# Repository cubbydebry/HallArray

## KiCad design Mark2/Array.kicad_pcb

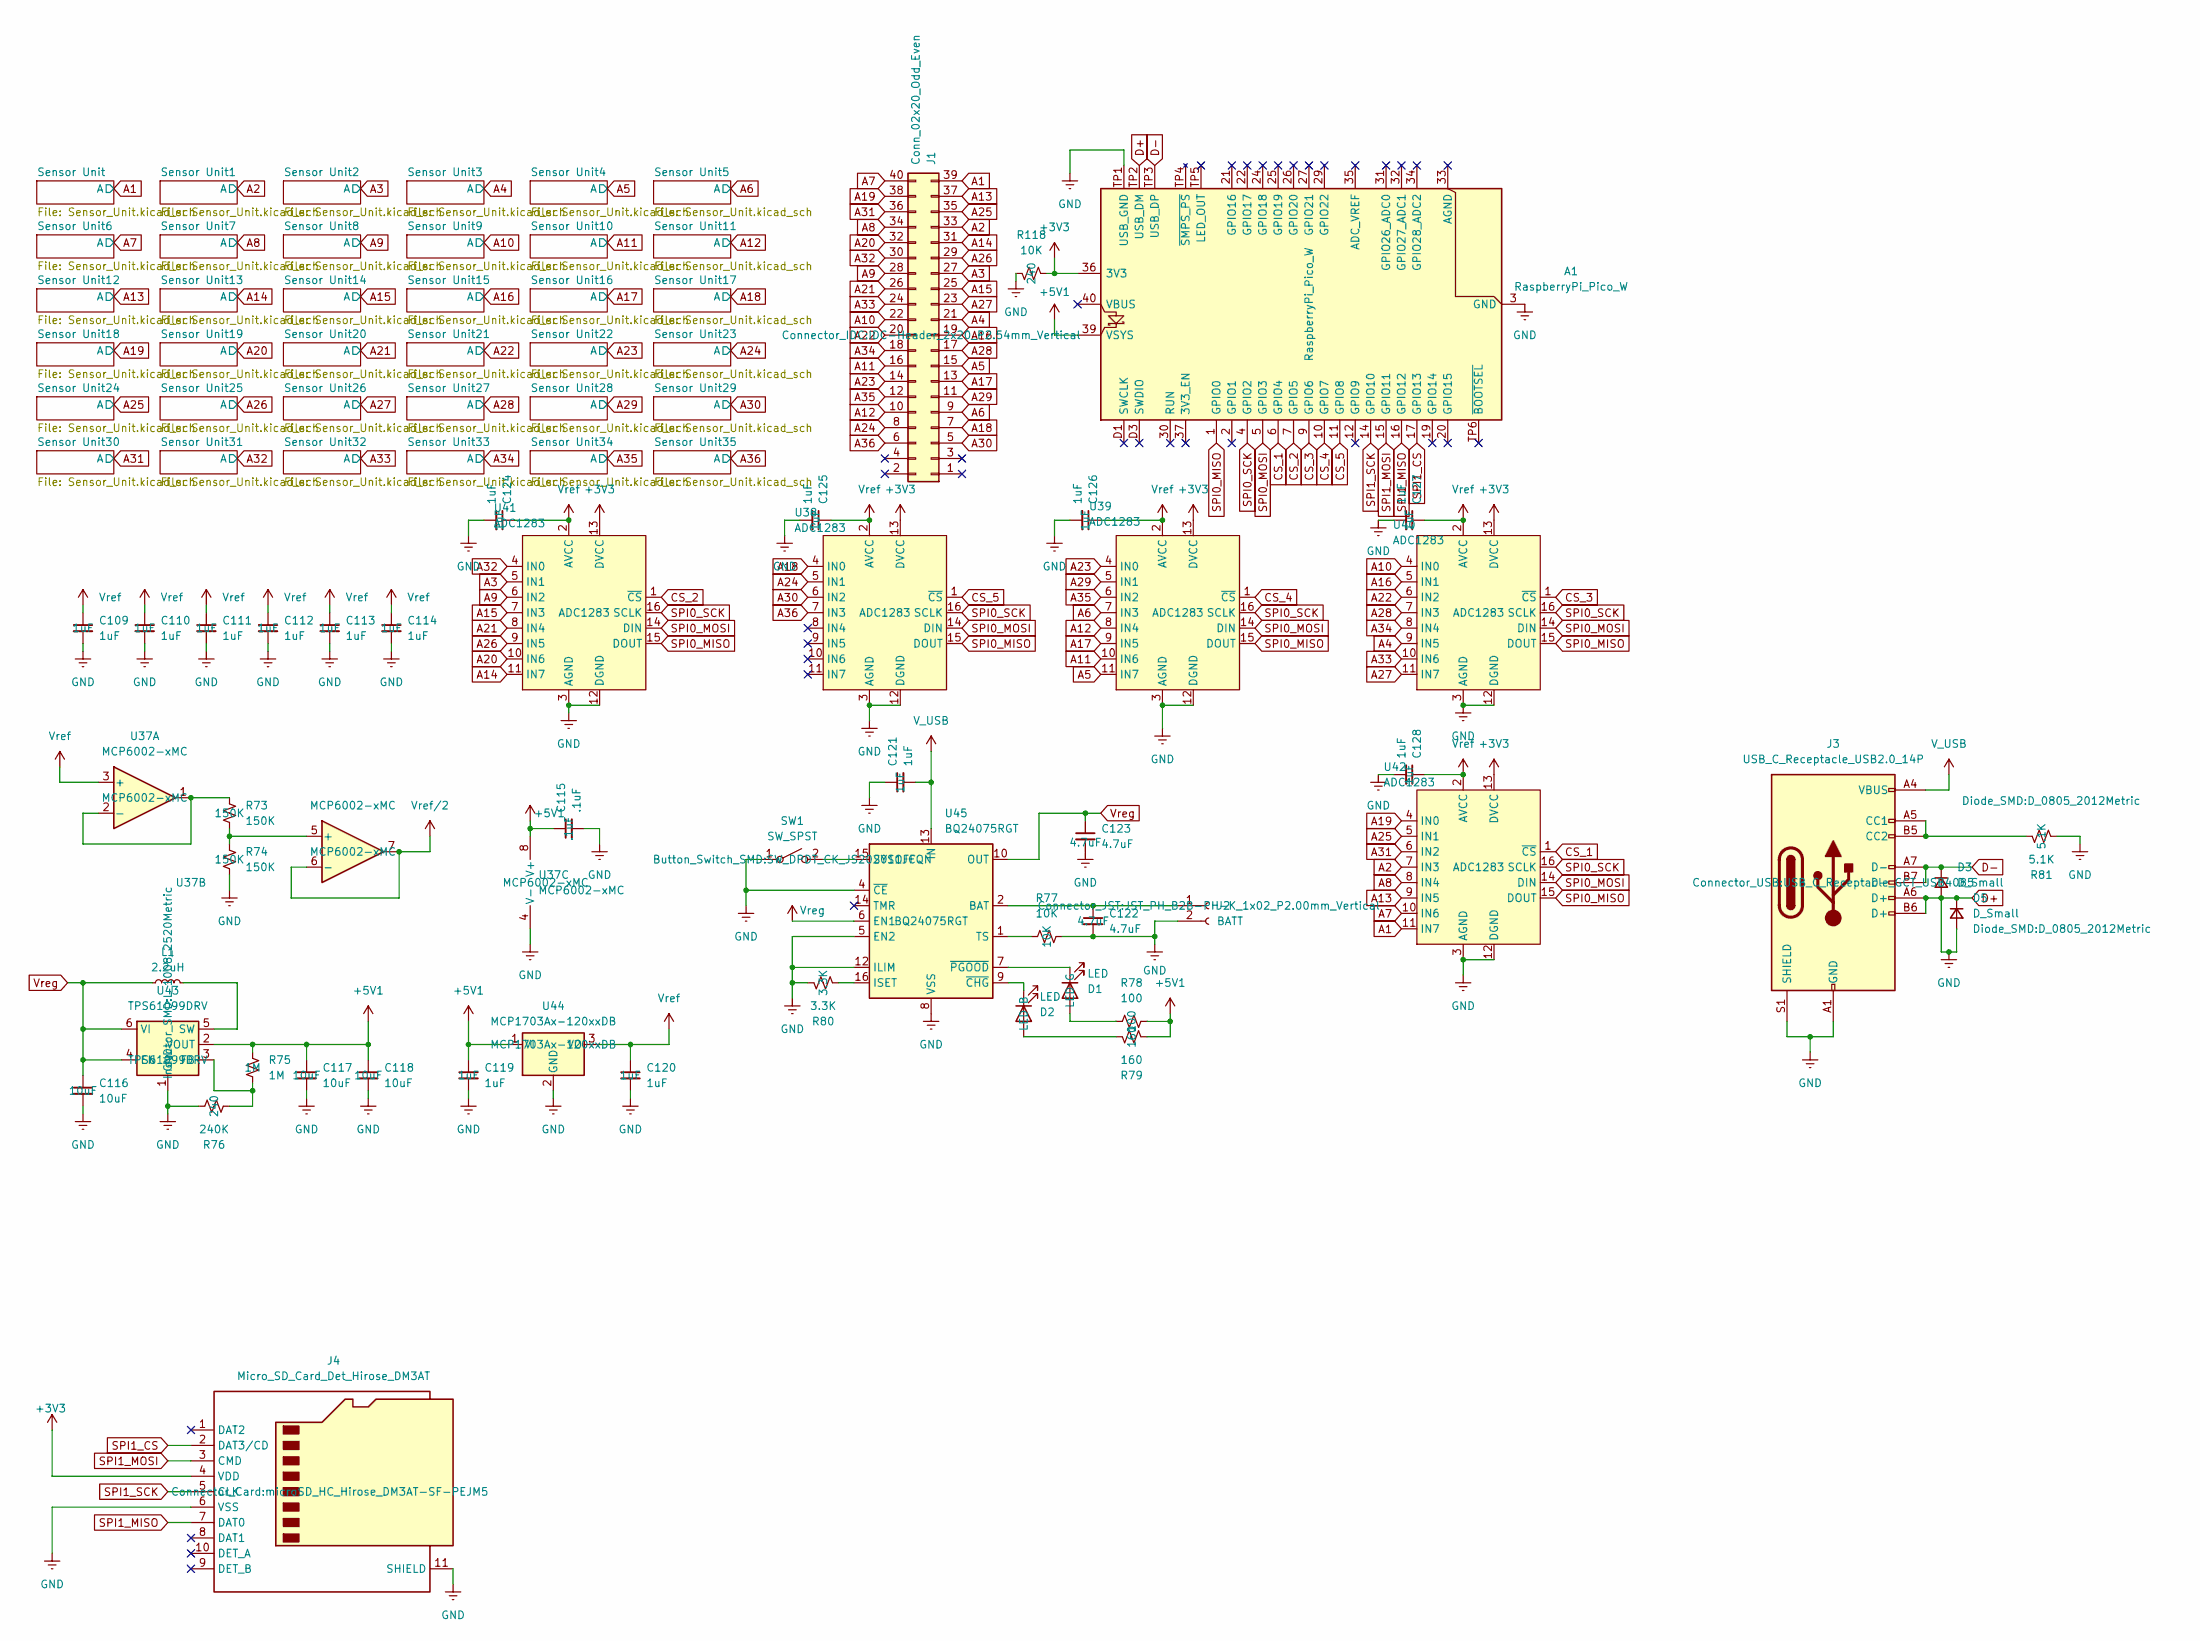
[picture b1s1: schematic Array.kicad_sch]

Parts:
A1: RaspberryPi_Pico_W; RaspberryPi_Pico_W_SMD; Part Number RaspberryPi_Pico_W
C109, C110, C111, C112, C113, C114, C119, C120, C121, C124, C125, C126, C127, C128: 1uF; C_0603_1608Metric; Part Number 1uF
C115: .1uF; C_0603_1608Metric; Part Number .1uF
C116, C117, C118: 10uF; C_0603_1608Metric; Part Number 10uF
C122, C123: 4.7uF; C_0603_1608Metric; Part Number 4.7uF
D1: LED; LED_0805_2012Metric; Part Number LED G
D2: LED; LED_0805_2012Metric; Part Number LED B
D3, D5: D_Small; D_0805_2012Metric; Part Number Diode_SMD:D_0805_2012Metric
J1: Conn_02x20_Odd_Even; IDC-Header_2x20_P2.54mm_Vertical; Part Number Connector_IDC:IDC-Header_2x20_P2.54mm_V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
J2: BATT; JST_PH_B2B-PH-K_1x02_P2.00mm_Vertical; Part Number Connector_JST:JST_PH_B2B-PH-K_1x02_P2.0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
J3: USB_C_Receptacle_USB2.0_14P; USB_C_Receptacle_GCT_USB4085; Part Number Connector_USB:USB_C_Receptacle_GCT_USB4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
J4: Micro_SD_Card_Det_Hirose_DM3AT; microSD_HC_Hirose_DM3AT-SF-PEJM5; Part Number Connector_Card:microSD_HC_Hirose_DM3AT-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
L1: 2.2uH; L_1008_2520Metric; Part Number Inductor_SMD:L_1008_2520Metric
R73, R74: 150K; R_0603_1608Metric; Part Number 150K
R75: 1M; R_0603_1608Metric; Part Number 1M
R76: 240K; R_0603_1608Metric; Part Number 240
R77: 10K; R_0603_1608Metric; Part Number 10K
R78: 100; R_0603_1608Metric; Part Number 100
R79: 160; R_0603_1608Metric; Part Number 160
R80: 3.3K; R_0603_1608Metric; Part Number 3.3K
R81: 5.1K; R_0603_1608Metric; Part Number 5.1K
R118: 10K; R_0603_1608Metric; Part Number 240
SW1: SW_SPST; SW_DPDT_CK_JS202011JCQN; Part Number Button_Switch_SMD:SW_DPDT_CK_JS202011JC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
U37: MCP6002-xMC; DFN-8-1EP_3x2mm_P0.5mm_EP1.75x1.45mm; Part Number MCP6002-xMC
U38, U39, U40, U41, U42: ADC1283; TSSOP-16_4.4x5mm_P0.65mm; Part Number ADC1283
U43: TPS61099DRV; WSON-6-1EP_2x2mm_P0.65mm_EP1x1.6mm; Part Number TPS61099DRV
U44: MCP1703Ax-120xxDB; SOT-223-3_TabPin2; Part Number MCP1703Ax-120xxDB
U45: BQ24075RGT; VQFN-16-1EP_3x3mm_P0.5mm_EP1.6x1.6mm; Part Number BQ24075RGT

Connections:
+3V3: A1.36 (3V3), J4.4 (VDD), R118.1, U38.13 (DVCC), U39.13 (DVCC), U40.13 (DVCC), U41.13 (DVCC), U42.13 (DVCC)
+5V1: A1.39 (VSYS), C115.1, C117.1, C118.1, C119.1, R75.1, R78.1, R79.1, U37.8 (V+), U43.2 (VOUT), U44.1 (VI)
A1: J1.39, U42.11 (IN7); also elsewhere on the board
A2: J1.33, U42.7 (IN3); also elsewhere on the board
A3: J1.27, U41.5 (IN1); also elsewhere on the board
A4: J1.21, U40.9 (IN5); also elsewhere on the board
A5: J1.15, U39.11 (IN7); also elsewhere on the board
A6: J1.9, U39.7 (IN3); also elsewhere on the board
A7: J1.40, U42.10 (IN6); also elsewhere on the board
A8: J1.34, U42.8 (IN4); also elsewhere on the board
A9: J1.28, U41.6 (IN2); also elsewhere on the board
A10: J1.22, U40.4 (IN0); also elsewhere on the board
A11: J1.16, U39.10 (IN6); also elsewhere on the board
A12: J1.10, U39.8 (IN4); also elsewhere on the board
A13: J1.37, U42.9 (IN5); also elsewhere on the board
A14: J1.31, U41.11 (IN7); also elsewhere on the board
A15: J1.25, U41.7 (IN3); also elsewhere on the board
A16: J1.19, U40.5 (IN1); also elsewhere on the board
A17: J1.13, U39.9 (IN5); also elsewhere on the board
A18: J1.7, U38.4 (IN0); also elsewhere on the board
A19: J1.38, U42.4 (IN0); also elsewhere on the board
A20: J1.32, U41.10 (IN6); also elsewhere on the board
A21: J1.26, U41.8 (IN4); also elsewhere on the board
A22: J1.20, U40.6 (IN2); also elsewhere on the board
A23: J1.14, U39.4 (IN0); also elsewhere on the board
A24: J1.8, U38.5 (IN1); also elsewhere on the board
A25: J1.35, U42.5 (IN1); also elsewhere on the board
A26: J1.29, U41.9 (IN5); also elsewhere on the board
A27: J1.23, U40.11 (IN7); also elsewhere on the board
A28: J1.17, U40.7 (IN3); also elsewhere on the board
A29: J1.11, U39.5 (IN1); also elsewhere on the board
A30: J1.5, U38.6 (IN2); also elsewhere on the board
A31: J1.36, U42.6 (IN2); also elsewhere on the board
A32: J1.30, U41.4 (IN0); also elsewhere on the board
A33: J1.24, U40.10 (IN6); also elsewhere on the board
A34: J1.18, U40.8 (IN4); also elsewhere on the board
A35: J1.12, U39.6 (IN2); also elsewhere on the board
A36: J1.6, U38.7 (IN3); also elsewhere on the board
CS_1: A1.6 (GPIO4), U42.1 (~CS)
CS_2: A1.7 (GPIO5), U41.1 (~CS)
CS_3: A1.9 (GPIO6), U40.1 (~CS)
CS_4: A1.10 (GPIO7), U39.1 (~CS)
CS_5: A1.11 (GPIO8), U38.1 (~CS)
unnamed: D1.2 (A), R78.2
unnamed: D1.1 (K), U45.7 (~PGOOD)
unnamed: D2.2 (A), R79.2
unnamed: D2.1 (K), U45.9 (~CHG)
unnamed: C122.1, J2.1, U45.2 (BAT), U45.3 (BAT)
unnamed: J3.A5 (CC1), J3.B5 (CC2), R81.2
unnamed: SW1.2 (B), U45.15 (SYSOFF)
unnamed: R73.1, U37.1, U37.2 (-)
unnamed: R73.2, R74.1, U37.5 (+)
unnamed: R75.2, R76.1, U43.3 (FB)
unnamed: L1.2, U43.5 (SW)
unnamed: R80.1, U45.16 (ISET)
unnamed: R77.2, U45.1 (TS)
SPI0_MISO: A1.1 (GPIO0), U38.15 (DOUT), U39.15 (DOUT), U40.15 (DOUT), U41.15 (DOUT), U42.15 (DOUT)
SPI0_MOSI: A1.5 (GPIO3), U38.14 (DIN), U39.14 (DIN), U40.14 (DIN), U41.14 (DIN), U42.14 (DIN)
SPI0_SCK: A1.4 (GPIO2), U38.16 (SCLK), U39.16 (SCLK), U40.16 (SCLK), U41.16 (SCLK), U42.16 (SCLK)
SPI1_CS: A1.17 (GPIO13), J4.2 (DAT3/CD)
SPI1_MISO: A1.16 (GPIO12), J4.7 (DAT0)
SPI1_MOSI: A1.15 (GPIO11), J4.3 (CMD)
SPI1_SCK: A1.14 (GPIO10), J4.5 (CLK)
V_USB: C121.2, J3.A4 (VBUS), J3.A9 (VBUS), J3.B4 (VBUS), J3.B9 (VBUS), U45.13 (IN)
Vref: C109.1, C110.1, C111.1, C112.1, C113.1, C114.1, C120.1, C124.1, C125.1, C126.1, C127.1, C128.1, U37.3 (+), U38.2 (AVCC), U39.2 (AVCC), U40.2 (AVCC), U41.2 (AVCC), U42.2 (AVCC), U44.3 (VO); also elsewhere on the board
Vref/2: U37.6 (-), U37.7; also elsewhere on the board
Vreg: C116.1, C123.1, L1.1, U43.4 (EN), U43.6 (VI), U45.6 (EN1), U45.10 (OUT), U45.11 (OUT)

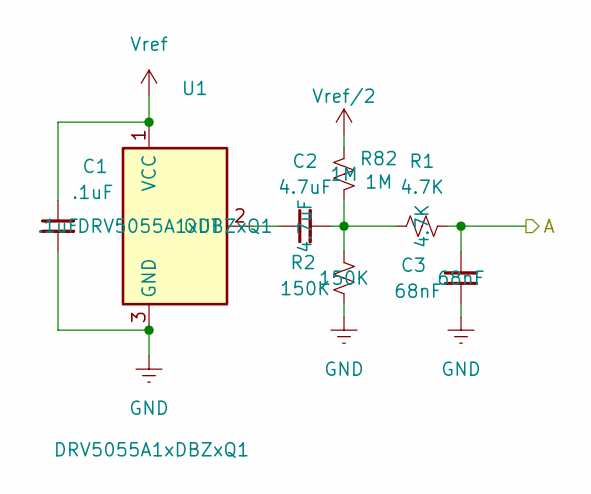
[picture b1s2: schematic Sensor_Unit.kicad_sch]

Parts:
C1: .1uF; C_0603_1608Metric; Part Number .1uF
C2: 4.7uF; C_0603_1608Metric; Part Number 4.7uF
C3: 68nF; C_0603_1608Metric; Part Number 68nF
R1: 4.7K; R_0603_1608Metric; Part Number 4.7K
R2: 150K; R_0603_1608Metric; Part Number 150K
R82: 1M; R_0603_1608Metric; Part Number 1M
U1: DRV5055A1xDBZxQ1; SOT-23; Part Number DRV5055A1xDBZxQ1

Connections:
A1: C3.2, R1.2; also elsewhere on the board
unnamed: C2.2, R1.1, R2.1, R82.2
unnamed: C2.1, U1.2 (OUT)
Vref: C1.1, U1.1 (VCC); also elsewhere on the board
Vref/2: R82.1; also elsewhere on the board

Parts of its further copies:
C4, C7, C10, C13, C16, C19, C20, C21, C22, C23, C24, C37, C38, C39, C40, C41, C42, C55, C56, C57, C58, C59, C60, C73, C74, C75, C76, C77, C78, C91, C92, C93, C94, C95, C96: .1uF; C_0603_1608Metric; Part Number .1uF
C5, C8, C11, C14, C17, C25, C26, C27, C28, C29, C30, C43, C44, C45, C46, C47, C48, C61, C62, C63, C64, C65, C66, C79, C80, C81, C82, C83, C84, C97, C98, C99, C100, C101, C102: 4.7uF; C_0603_1608Metric; Part Number 4.7uF
C6, C9, C12, C15, C18, C31, C32, C33, C34, C35, C36, C49, C50, C51, C52, C53, C54, C67, C68, C69, C70, C71, C72, C85, C86, C87, C88, C89, C90, C103, C104, C105, C106, C107, C108: 68nF; C_0603_1608Metric; Part Number 68nF
R3, R5, R7, R9, R11, R13, R14, R15, R16, R17, R18, R25, R26, R27, R28, R29, R30, R37, R38, R39, R40, R41, R42, R49, R50, R51, R52, R53, R54, R61, R62, R63, R64, R65, R66: 150K; R_0603_1608Metric; Part Number 150K
R4, R6, R8, R10, R12, R19, R20, R21, R22, R23, R24, R31, R32, R33, R34, R35, R36, R43, R44, R45, R46, R47, R48, R55, R56, R57, R58, R59, R60, R67, R68, R69, R70, R71, R72: 4.7K; R_0603_1608Metric; Part Number 4.7K
R83, R84, R85, R86, R87, R88, R89, R90, R91, R92, R93, R94, R95, R96, R97, R98, R99, R100, R101, R102, R103, R104, R105, R106, R107, R108, R109, R110, R111, R112, R113, R114, R115, R116, R117: 1M; R_0603_1608Metric; Part Number 1M
U2, U3, U4, U5, U6, U7, U8, U9, U10, U11, U12, U13, U14, U15, U16, U17, U18, U19, U20, U21, U22, U23, U24, U25, U26, U27, U28, U29, U30, U31, U32, U33, U34, U35, U36: DRV5055A1xDBZxQ1; SOT-23; Part Number DRV5055A1xDBZxQ1

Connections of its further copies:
A2: C6.2, R4.2; also elsewhere on the board
A3: C9.2, R6.2; also elsewhere on the board
A4: C12.2, R8.2; also elsewhere on the board
A5: C15.2, R10.2; also elsewhere on the board
A6: C18.2, R12.2; also elsewhere on the board
A7: C31.2, R19.2; also elsewhere on the board
A8: C32.2, R23.2; also elsewhere on the board
A9: C33.2, R21.2; also elsewhere on the board
A10: C34.2, R20.2; also elsewhere on the board
A11: C35.2, R22.2; also elsewhere on the board
A12: C36.2, R24.2; also elsewhere on the board
A13: C49.2, R31.2; also elsewhere on the board
A14: C50.2, R35.2; also elsewhere on the board
A15: C51.2, R33.2; also elsewhere on the board
A16: C52.2, R32.2; also elsewhere on the board
A17: C53.2, R34.2; also elsewhere on the board
A18: C54.2, R36.2; also elsewhere on the board
A19: C67.2, R43.2; also elsewhere on the board
A20: C68.2, R47.2; also elsewhere on the board
A21: C69.2, R45.2; also elsewhere on the board
A22: C70.2, R44.2; also elsewhere on the board
A23: C71.2, R46.2; also elsewhere on the board
A24: C72.2, R48.2; also elsewhere on the board
A25: C85.2, R55.2; also elsewhere on the board
A26: C86.2, R59.2; also elsewhere on the board
A27: C87.2, R57.2; also elsewhere on the board
A28: C88.2, R56.2; also elsewhere on the board
A29: C89.2, R58.2; also elsewhere on the board
A30: C90.2, R60.2; also elsewhere on the board
A31: C103.2, R67.2; also elsewhere on the board
A32: C104.2, R71.2; also elsewhere on the board
A33: C105.2, R69.2; also elsewhere on the board
A34: C106.2, R68.2; also elsewhere on the board
A35: C107.2, R70.2; also elsewhere on the board
A36: C108.2, R72.2; also elsewhere on the board
unnamed: C5.2, R3.1, R4.1, R83.2
unnamed: C8.2, R5.1, R6.1, R84.2
unnamed: C11.2, R7.1, R8.1, R85.2
unnamed: C14.2, R9.1, R10.1, R86.2
unnamed: C17.2, R11.1, R12.1, R87.2
unnamed: C25.2, R15.1, R23.1, R89.2
unnamed: C26.2, R17.1, R21.1, R90.2
unnamed: C27.2, R13.1, R20.1, R91.2
unnamed: C28.2, R18.1, R22.1, R92.2
unnamed: C29.2, R16.1, R24.1, R93.2
unnamed: C30.2, R14.1, R19.1, R88.2
unnamed: C43.2, R27.1, R35.1, R95.2
unnamed: C44.2, R29.1, R33.1, R96.2
unnamed: C45.2, R25.1, R32.1, R97.2
unnamed: C46.2, R30.1, R34.1, R98.2
unnamed: C47.2, R28.1, R36.1, R99.2
unnamed: C48.2, R26.1, R31.1, R94.2
unnamed: C61.2, R39.1, R47.1, R101.2
unnamed: C62.2, R41.1, R45.1, R102.2
unnamed: C63.2, R37.1, R44.1, R103.2
unnamed: C64.2, R42.1, R46.1, R104.2
unnamed: C65.2, R40.1, R48.1, R105.2
unnamed: C66.2, R38.1, R43.1, R100.2
unnamed: C79.2, R51.1, R59.1, R107.2
unnamed: C80.2, R53.1, R57.1, R108.2
unnamed: C81.2, R49.1, R56.1, R109.2
unnamed: C82.2, R54.1, R58.1, R110.2
unnamed: C83.2, R52.1, R60.1, R111.2
unnamed: C84.2, R50.1, R55.1, R106.2
unnamed: C97.2, R63.1, R71.1, R113.2
unnamed: C98.2, R65.1, R69.1, R114.2
unnamed: C99.2, R61.1, R68.1, R115.2
unnamed: C100.2, R66.1, R70.1, R116.2
unnamed: C101.2, R64.1, R72.1, R117.2
unnamed: C102.2, R62.1, R67.1, R112.2
unnamed: C5.1, U2.2 (OUT)
unnamed: C8.1, U3.2 (OUT)
unnamed: C11.1, U4.2 (OUT)
unnamed: C14.1, U5.2 (OUT)
unnamed: C17.1, U6.2 (OUT)
unnamed: C30.1, U7.2 (OUT)
unnamed: C25.1, U8.2 (OUT)
unnamed: C26.1, U9.2 (OUT)
unnamed: C27.1, U10.2 (OUT)
unnamed: C28.1, U11.2 (OUT)
unnamed: C29.1, U12.2 (OUT)
unnamed: C48.1, U13.2 (OUT)
unnamed: C43.1, U14.2 (OUT)
unnamed: C44.1, U15.2 (OUT)
unnamed: C45.1, U16.2 (OUT)
unnamed: C46.1, U17.2 (OUT)
unnamed: C47.1, U18.2 (OUT)
unnamed: C66.1, U19.2 (OUT)
unnamed: C61.1, U20.2 (OUT)
unnamed: C62.1, U21.2 (OUT)
unnamed: C63.1, U22.2 (OUT)
unnamed: C64.1, U23.2 (OUT)
unnamed: C65.1, U24.2 (OUT)
unnamed: C84.1, U25.2 (OUT)
unnamed: C79.1, U26.2 (OUT)
unnamed: C80.1, U27.2 (OUT)
unnamed: C81.1, U28.2 (OUT)
unnamed: C82.1, U29.2 (OUT)
unnamed: C83.1, U30.2 (OUT)
unnamed: C102.1, U31.2 (OUT)
unnamed: C97.1, U32.2 (OUT)
unnamed: C98.1, U33.2 (OUT)
unnamed: C99.1, U34.2 (OUT)
unnamed: C100.1, U35.2 (OUT)
unnamed: C101.1, U36.2 (OUT)
Vref: C4.1, C7.1, C10.1, C13.1, C16.1, C19.1, C20.1, C21.1, C22.1, C23.1, C24.1, C37.1, C38.1, C39.1, C40.1, C41.1, C42.1, C55.1, C56.1, C57.1, C58.1, C59.1, C60.1, C73.1, C74.1, C75.1, C76.1, C77.1, C78.1, C91.1, C92.1, C93.1, C94.1, C95.1, C96.1, U2.1 (VCC), U3.1 (VCC), U4.1 (VCC), U5.1 (VCC), U6.1 (VCC), U7.1 (VCC), U8.1 (VCC), U9.1 (VCC), U10.1 (VCC), U11.1 (VCC), U12.1 (VCC), U13.1 (VCC), U14.1 (VCC), U15.1 (VCC), U16.1 (VCC), U17.1 (VCC), U18.1 (VCC), U19.1 (VCC), U20.1 (VCC), U21.1 (VCC), U22.1 (VCC), U23.1 (VCC), U24.1 (VCC), U25.1 (VCC), U26.1 (VCC), U27.1 (VCC), U28.1 (VCC), U29.1 (VCC), U30.1 (VCC), U31.1 (VCC), U32.1 (VCC), U33.1 (VCC), U34.1 (VCC), U35.1 (VCC), U36.1 (VCC); also elsewhere on the board
Vref/2: R83.1, R84.1, R85.1, R86.1, R87.1, R88.1, R89.1, R90.1, R91.1, R92.1, R93.1, R94.1, R95.1, R96.1, R97.1, R98.1, R99.1, R100.1, R101.1, R102.1, R103.1, R104.1, R105.1, R106.1, R107.1, R108.1, R109.1, R110.1, R111.1, R112.1, R113.1, R114.1, R115.1, R116.1, R117.1; also elsewhere on the board

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
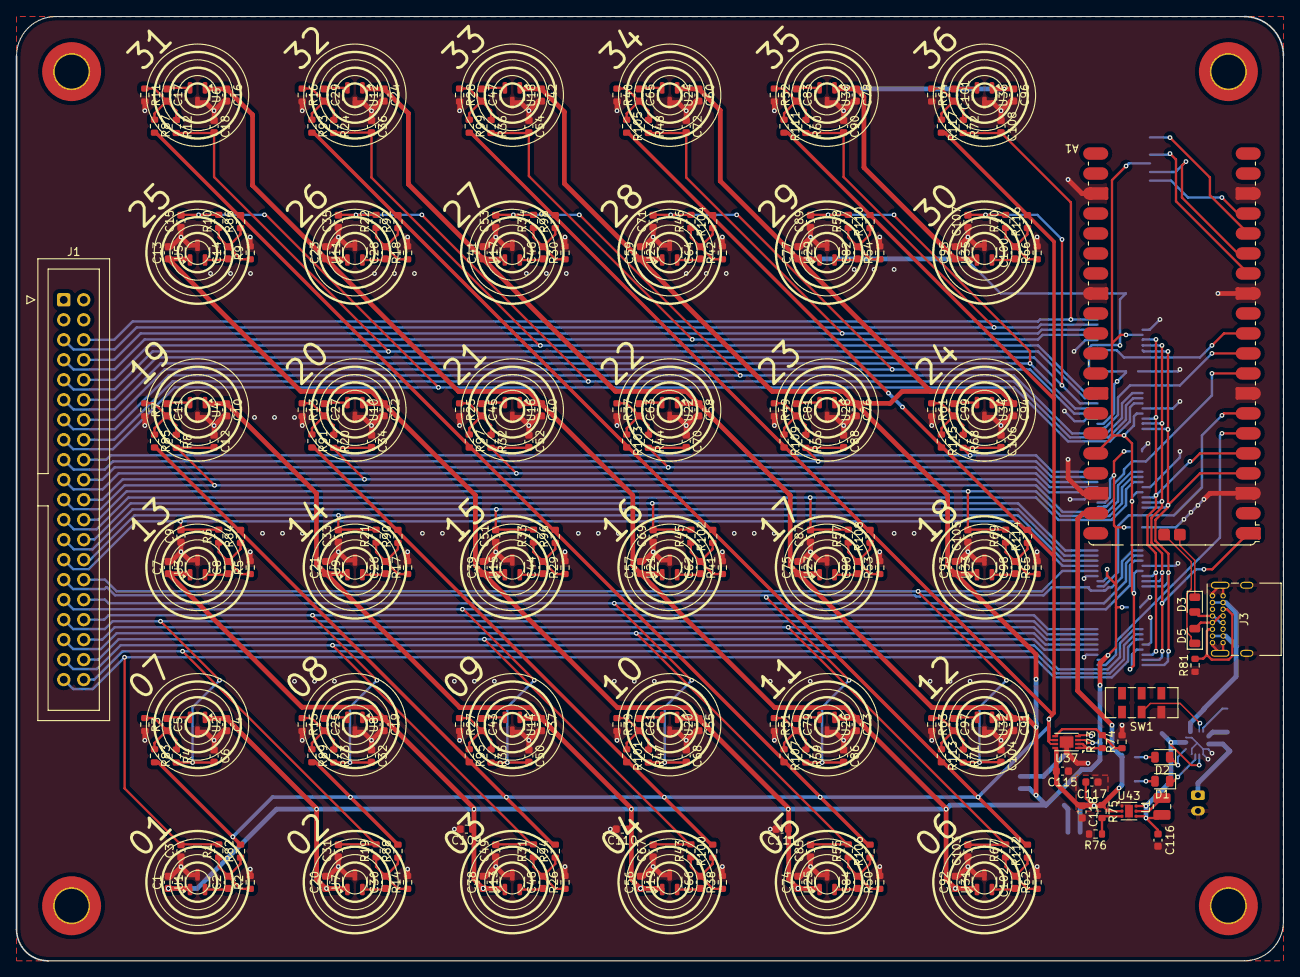
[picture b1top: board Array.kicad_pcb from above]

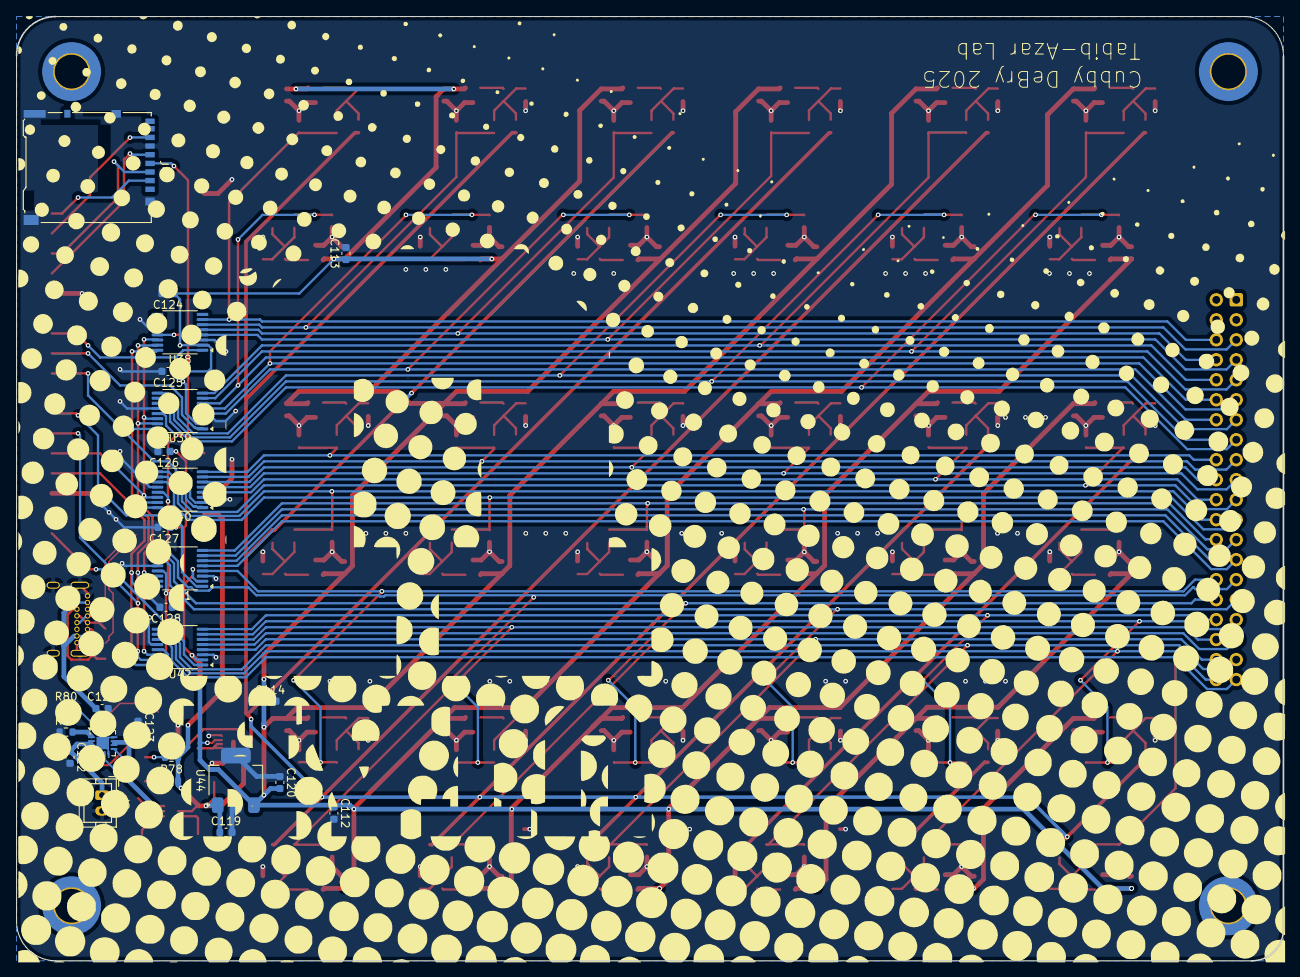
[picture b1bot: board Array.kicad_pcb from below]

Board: 2 copper layers, 161.0 x 120.0 mm, 301 parts (26 on the bottom side), 144 nets.

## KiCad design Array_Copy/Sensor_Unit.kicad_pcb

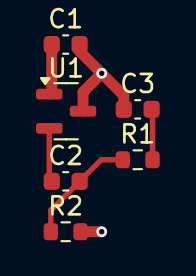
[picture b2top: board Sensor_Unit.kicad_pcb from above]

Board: 2 copper layers, 6 parts (0 on the bottom side), 5 nets.

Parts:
C1: .1uF; C_0603_1608Metric
C2: 1uF; C_0603_1608Metric
C3: 68nF; C_0603_1608Metric
R1: 4.7K; R_0603_1608Metric
R2: 150K; R_0603_1608Metric
U1: DRV5055A1xDBZxQ1; SOT-23

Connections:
+3V3: C1.1, U1.1 (VCC)
A1: C3.2, R1.2
GND: C1.2, C3.1, R2.2, U1.3 (GND)
unnamed: C2.1, U1.2 (OUT)
Vref/2: C2.2, R1.1, R2.1

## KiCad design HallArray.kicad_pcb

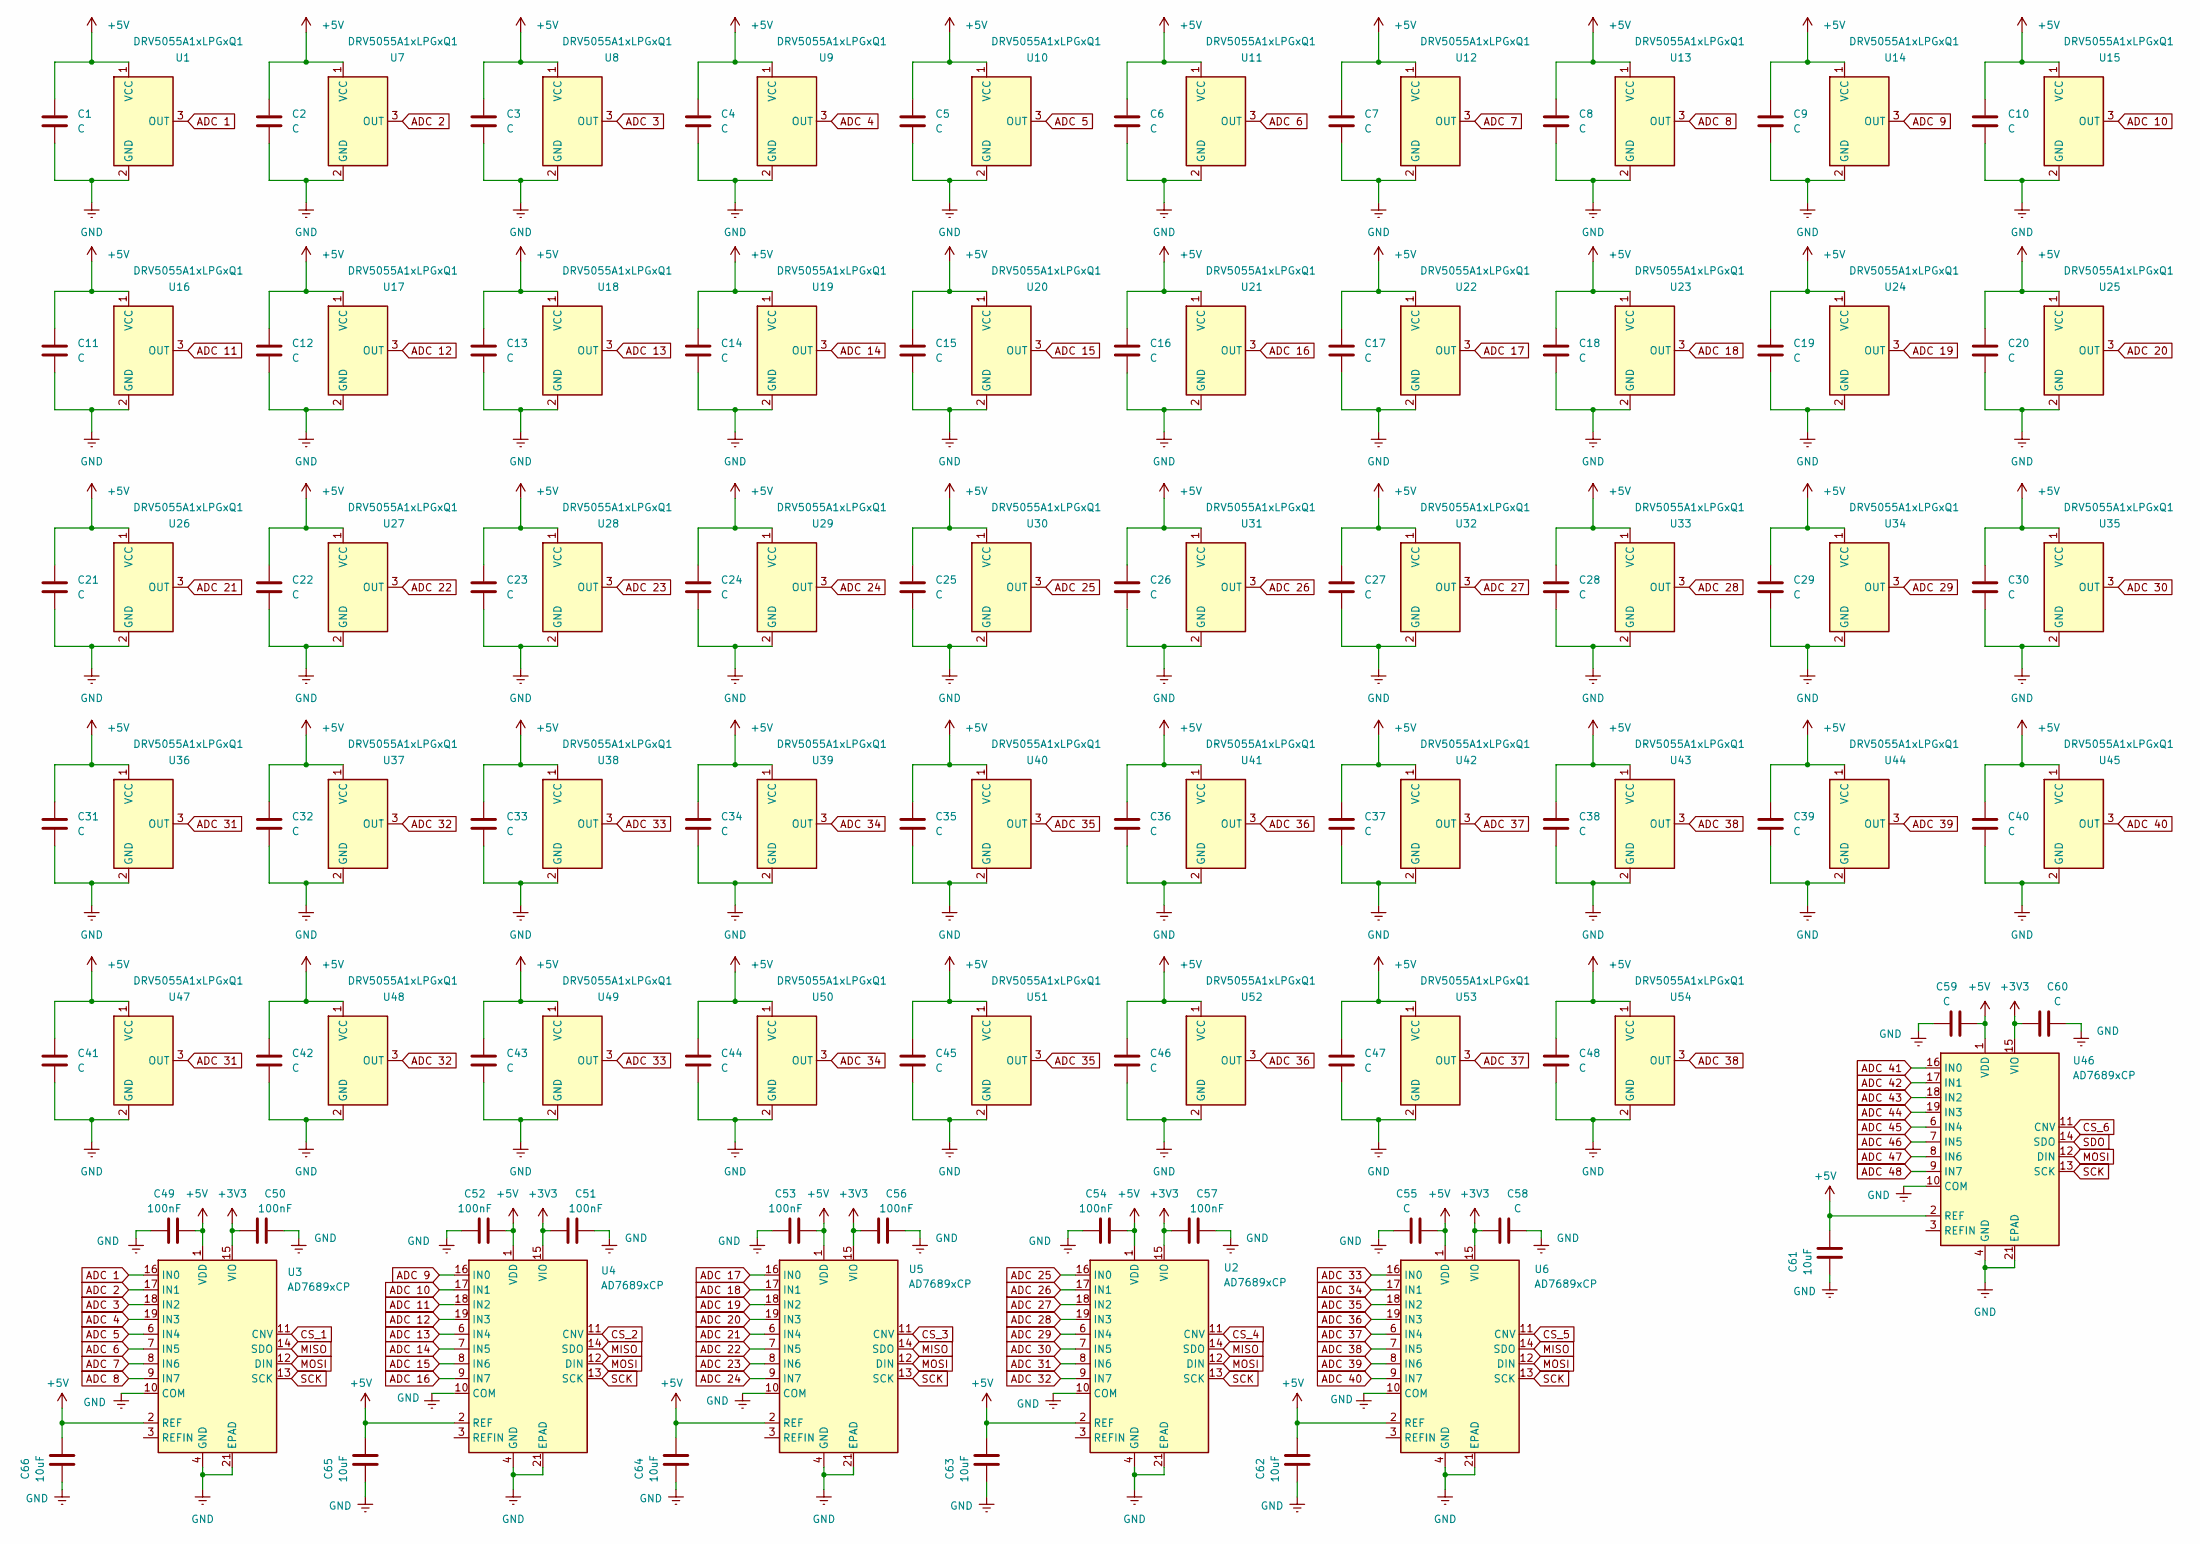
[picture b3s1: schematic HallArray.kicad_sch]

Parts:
C1, C2, C3, C4, C5, C6, C7, C8, C9, C10, C11, C12, C13, C14, C15, C16, C17, C18, C19, C20, C21, C22, C23, C24, C25, C26, C27, C28, C29, C30, C31, C32, C33, C34, C35, C36, C37, C38, C39, C40, C41, C42, C43, C44, C45, C46, C47, C48, C55, C58, C59, C60: C; C_0603_1608Metric
C49, C50, C51, C52, C53, C54, C56, C57: 100nF; C_0603_1608Metric
C61, C62, C63, C64, C65, C66: 10uF; C_0603_1608Metric
U1, U7, U8, U9, U10, U11, U12, U13, U14, U15, U16, U17, U18, U19, U20, U21, U22, U23, U24, U25, U26, U27, U28, U29, U30, U31, U32, U33, U34, U35, U36, U37, U38, U39, U40, U41, U42, U43, U44, U45, U47, U48, U49, U50, U51, U52, U53, U54: DRV5055A1xLPGxQ1; TO-92_Inline
U2, U3, U4, U5, U6, U46: AD7689xCP; LFCSP-20-1EP_4x4mm_P0.5mm_EP2.5x2.5mm

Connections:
+3V3: C50.1, C51.1, C56.1, C57.1, C58.1, C60.1, U2.15 (VIO), U3.15 (VIO), U4.15 (VIO), U5.15 (VIO), U6.15 (VIO), U46.15 (VIO)
+5V: C1.1, C2.1, C3.1, C4.1, C5.1, C6.1, C7.1, C8.1, C9.1, C10.1, C11.1, C12.1, C13.1, C14.1, C15.1, C16.1, C17.1, C18.1, C19.1, C20.1, C21.1, C22.1, C23.1, C24.1, C25.1, C26.1, C27.1, C28.1, C29.1, C30.1, C31.1, C32.1, C33.1, C34.1, C35.1, C36.1, C37.1, C38.1, C39.1, C40.1, C41.1, C42.1, C43.1, C44.1, C45.1, C46.1, C47.1, C48.1, C49.2, C52.2, C53.2, C54.2, C55.2, C59.2, C61.2, C62.2, C63.2, C64.2, C65.2, C66.2, U1.1 (VCC), U2.1 (VDD), U2.2 (REF), U2.20 (VDD), U3.1 (VDD), U3.2 (REF), U3.20 (VDD), U4.1 (VDD), U4.2 (REF), U4.20 (VDD), U5.1 (VDD), U5.2 (REF), U5.20 (VDD), U6.1 (VDD), U6.2 (REF), U6.20 (VDD), U7.1 (VCC), U8.1 (VCC), U9.1 (VCC), U10.1 (VCC), U11.1 (VCC), U12.1 (VCC), U13.1 (VCC), U14.1 (VCC), U15.1 (VCC), U16.1 (VCC), U17.1 (VCC), U18.1 (VCC), U19.1 (VCC), U20.1 (VCC), U21.1 (VCC), U22.1 (VCC), U23.1 (VCC), U24.1 (VCC), U25.1 (VCC), U26.1 (VCC), U27.1 (VCC), U28.1 (VCC), U29.1 (VCC), U30.1 (VCC), U31.1 (VCC), U32.1 (VCC), U33.1 (VCC), U34.1 (VCC), U35.1 (VCC), U36.1 (VCC), U37.1 (VCC), U38.1 (VCC), U39.1 (VCC), U40.1 (VCC), U41.1 (VCC), U42.1 (VCC), U43.1 (VCC), U44.1 (VCC), U45.1 (VCC), U46.1 (VDD), U46.2 (REF), U46.20 (VDD), U47.1 (VCC), U48.1 (VCC), U49.1 (VCC), U50.1 (VCC), U51.1 (VCC), U52.1 (VCC), U53.1 (VCC), U54.1 (VCC)
ADC 1: U1.3 (OUT), U3.16 (IN0)
ADC 2: U3.17 (IN1), U7.3 (OUT)
ADC 3: U3.18 (IN2), U8.3 (OUT)
ADC 4: U3.19 (IN3), U9.3 (OUT)
ADC 5: U3.6 (IN4), U10.3 (OUT)
ADC 6: U3.7 (IN5), U11.3 (OUT)
ADC 7: U3.8 (IN6), U12.3 (OUT)
ADC 8: U3.9 (IN7), U13.3 (OUT)
ADC 9: U4.16 (IN0), U14.3 (OUT)
ADC 10: U4.17 (IN1), U15.3 (OUT)
ADC 11: U4.18 (IN2), U16.3 (OUT)
ADC 12: U4.19 (IN3), U17.3 (OUT)
ADC 13: U4.6 (IN4), U18.3 (OUT)
ADC 14: U4.7 (IN5), U19.3 (OUT)
ADC 15: U4.8 (IN6), U20.3 (OUT)
ADC 16: U4.9 (IN7), U21.3 (OUT)
ADC 17: U5.16 (IN0), U22.3 (OUT)
ADC 18: U5.17 (IN1), U23.3 (OUT)
ADC 19: U5.18 (IN2), U24.3 (OUT)
ADC 20: U5.19 (IN3), U25.3 (OUT)
ADC 21: U5.6 (IN4), U26.3 (OUT)
ADC 22: U5.7 (IN5), U27.3 (OUT)
ADC 23: U5.8 (IN6), U28.3 (OUT)
ADC 24: U5.9 (IN7), U29.3 (OUT)
ADC 25: U2.16 (IN0), U30.3 (OUT)
ADC 26: U2.17 (IN1), U31.3 (OUT)
ADC 27: U2.18 (IN2), U32.3 (OUT)
ADC 28: U2.19 (IN3), U33.3 (OUT)
ADC 29: U2.6 (IN4), U34.3 (OUT)
ADC 30: U2.7 (IN5), U35.3 (OUT)
ADC 31: U2.8 (IN6), U36.3 (OUT), U47.3 (OUT)
ADC 32: U2.9 (IN7), U37.3 (OUT), U48.3 (OUT)
ADC 33: U6.16 (IN0), U38.3 (OUT), U49.3 (OUT)
ADC 34: U6.17 (IN1), U39.3 (OUT), U50.3 (OUT)
ADC 35: U6.18 (IN2), U40.3 (OUT), U51.3 (OUT)
ADC 36: U6.19 (IN3), U41.3 (OUT), U52.3 (OUT)
ADC 37: U6.6 (IN4), U42.3 (OUT), U53.3 (OUT)
ADC 38: U6.7 (IN5), U43.3 (OUT), U54.3 (OUT)
ADC 39: U6.8 (IN6), U44.3 (OUT)
ADC 40: U6.9 (IN7), U45.3 (OUT)
ADC 41: U46.16 (IN0)
ADC 42: U46.17 (IN1)
ADC 43: U46.18 (IN2)
ADC 44: U46.19 (IN3)
ADC 45: U46.6 (IN4)
ADC 46: U46.7 (IN5)
ADC 47: U46.8 (IN6)
ADC 48: U46.9 (IN7)
CS_1: U3.11 (CNV)
CS_2: U4.11 (CNV)
CS_3: U5.11 (CNV)
CS_4: U2.11 (CNV)
CS_5: U6.11 (CNV)
CS_6: U46.11 (CNV)
GND: C1.2, C2.2, C3.2, C4.2, C5.2, C6.2, C7.2, C8.2, C9.2, C10.2, C11.2, C12.2, C13.2, C14.2, C15.2, C16.2, C17.2, C18.2, C19.2, C20.2, C21.2, C22.2, C23.2, C24.2, C25.2, C26.2, C27.2, C28.2, C29.2, C30.2, C31.2, C32.2, C33.2, C34.2, C35.2, C36.2, C37.2, C38.2, C39.2, C40.2, C41.2, C42.2, C43.2, C44.2, C45.2, C46.2, C47.2, C48.2, C49.1, C50.2, C51.2, C52.1, C53.1, C54.1, C55.1, C56.2, C57.2, C58.2, C59.1, C60.2, C61.1, C62.1, C63.1, C64.1, C65.1, C66.1, U1.2 (GND), U2.4 (GND), U2.5 (GND), U2.10 (COM), U2.21 (EPAD), U3.4 (GND), U3.5 (GND), U3.10 (COM), U3.21 (EPAD), U4.4 (GND), U4.5 (GND), U4.10 (COM), U4.21 (EPAD), U5.4 (GND), U5.5 (GND), U5.10 (COM), U5.21 (EPAD), U6.4 (GND), U6.5 (GND), U6.10 (COM), U6.21 (EPAD), U7.2 (GND), U8.2 (GND), U9.2 (GND), U10.2 (GND), U11.2 (GND), U12.2 (GND), U13.2 (GND), U14.2 (GND), U15.2 (GND), U16.2 (GND), U17.2 (GND), U18.2 (GND), U19.2 (GND), U20.2 (GND), U21.2 (GND), U22.2 (GND), U23.2 (GND), U24.2 (GND), U25.2 (GND), U26.2 (GND), U27.2 (GND), U28.2 (GND), U29.2 (GND), U30.2 (GND), U31.2 (GND), U32.2 (GND), U33.2 (GND), U34.2 (GND), U35.2 (GND), U36.2 (GND), U37.2 (GND), U38.2 (GND), U39.2 (GND), U40.2 (GND), U41.2 (GND), U42.2 (GND), U43.2 (GND), U44.2 (GND), U45.2 (GND), U46.4 (GND), U46.5 (GND), U46.10 (COM), U46.21 (EPAD), U47.2 (GND), U48.2 (GND), U49.2 (GND), U50.2 (GND), U51.2 (GND), U52.2 (GND), U53.2 (GND), U54.2 (GND)
MISO: U2.14 (SDO), U3.14 (SDO), U4.14 (SDO), U5.14 (SDO), U6.14 (SDO)
MOSI: U2.12 (DIN), U3.12 (DIN), U4.12 (DIN), U5.12 (DIN), U6.12 (DIN), U46.12 (DIN)
SCK: U2.13 (SCK), U3.13 (SCK), U4.13 (SCK), U5.13 (SCK), U6.13 (SCK), U46.13 (SCK)
SDO: U46.14 (SDO)

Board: 2 copper layers, 120 parts (0 on the bottom side), 46 nets, no tracks yet.

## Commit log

2025-09-24 Removed submodules
2025-09-24 Fixed submodules
2025-09-29 Added rolling average.
2025-10-01 Created python script for basic plotting.
2025-10-02 Added PSD plot
2025-10-02 Timing fixes
2025-10-14 Added script to compute PSD of xls file
2025-12-09 New scripts
